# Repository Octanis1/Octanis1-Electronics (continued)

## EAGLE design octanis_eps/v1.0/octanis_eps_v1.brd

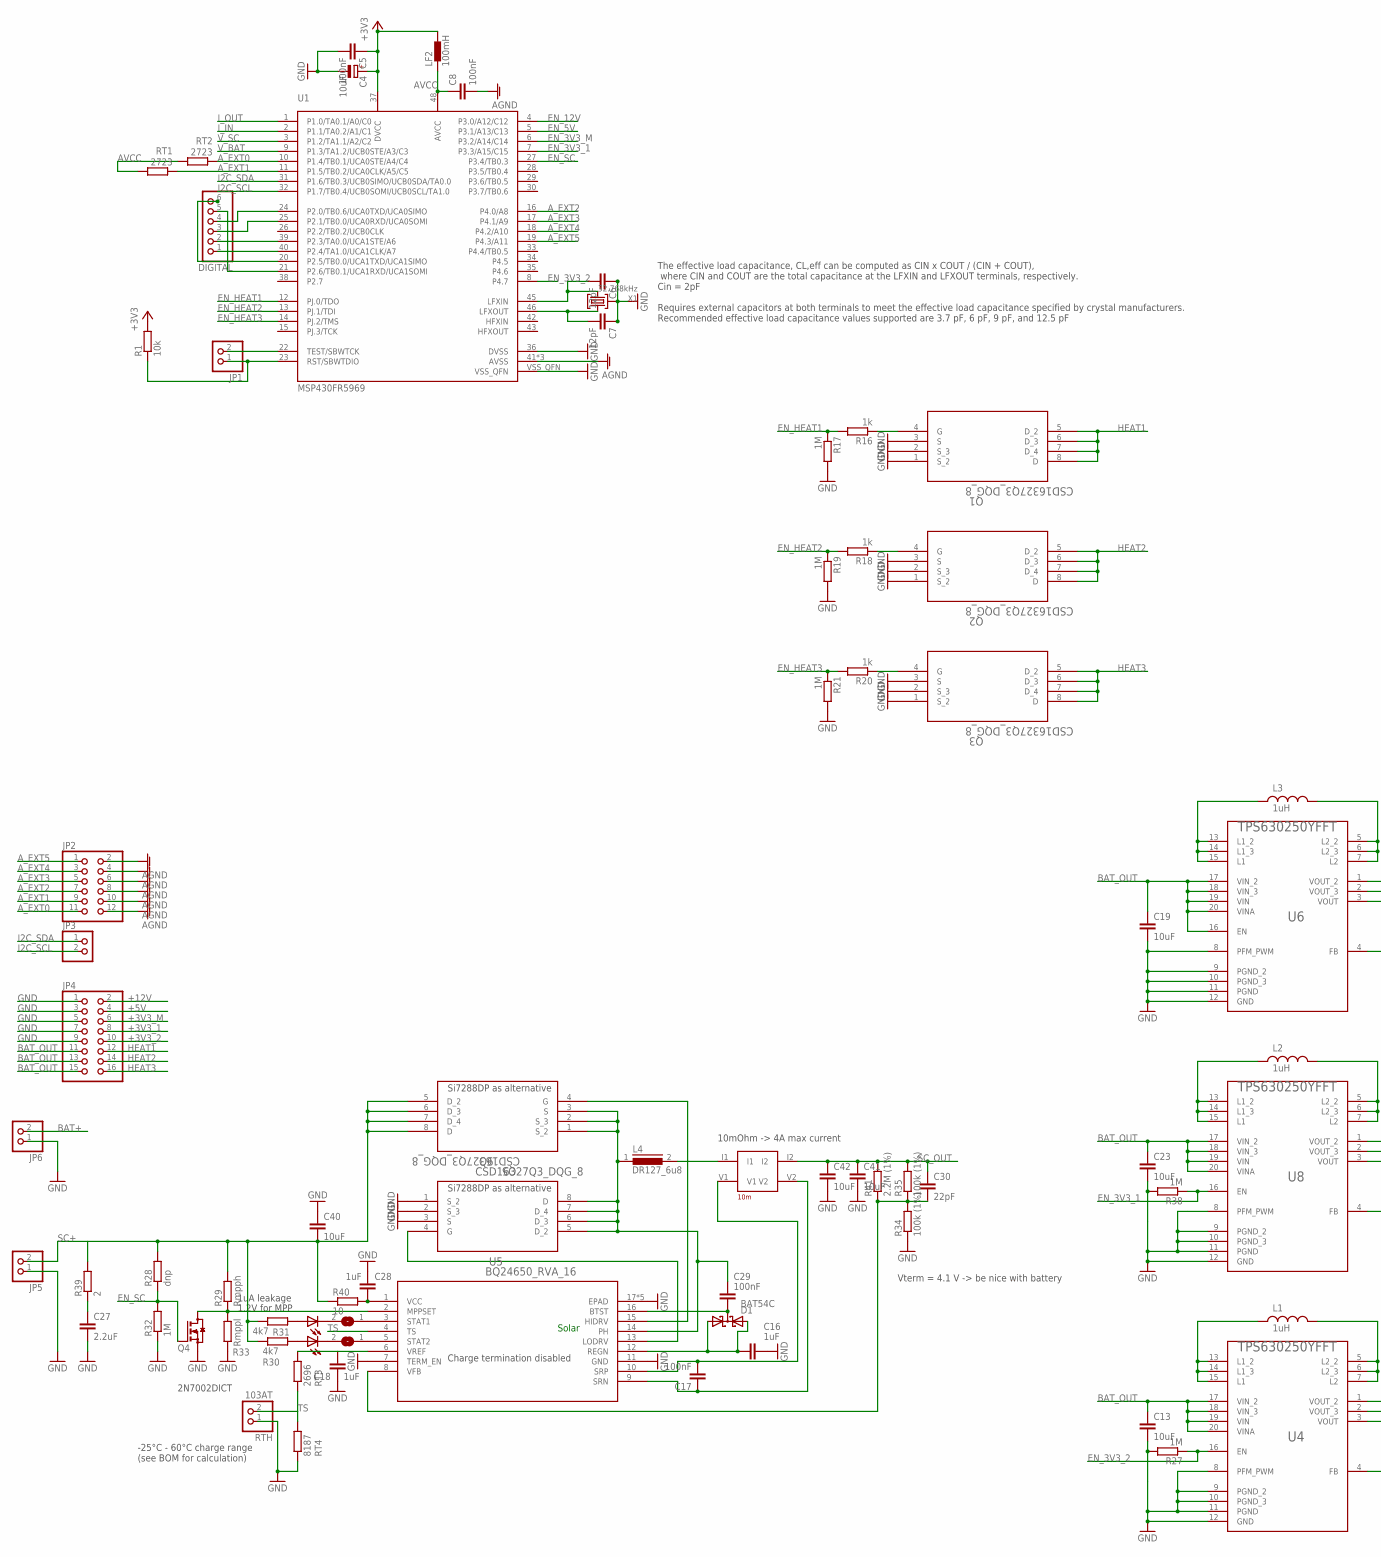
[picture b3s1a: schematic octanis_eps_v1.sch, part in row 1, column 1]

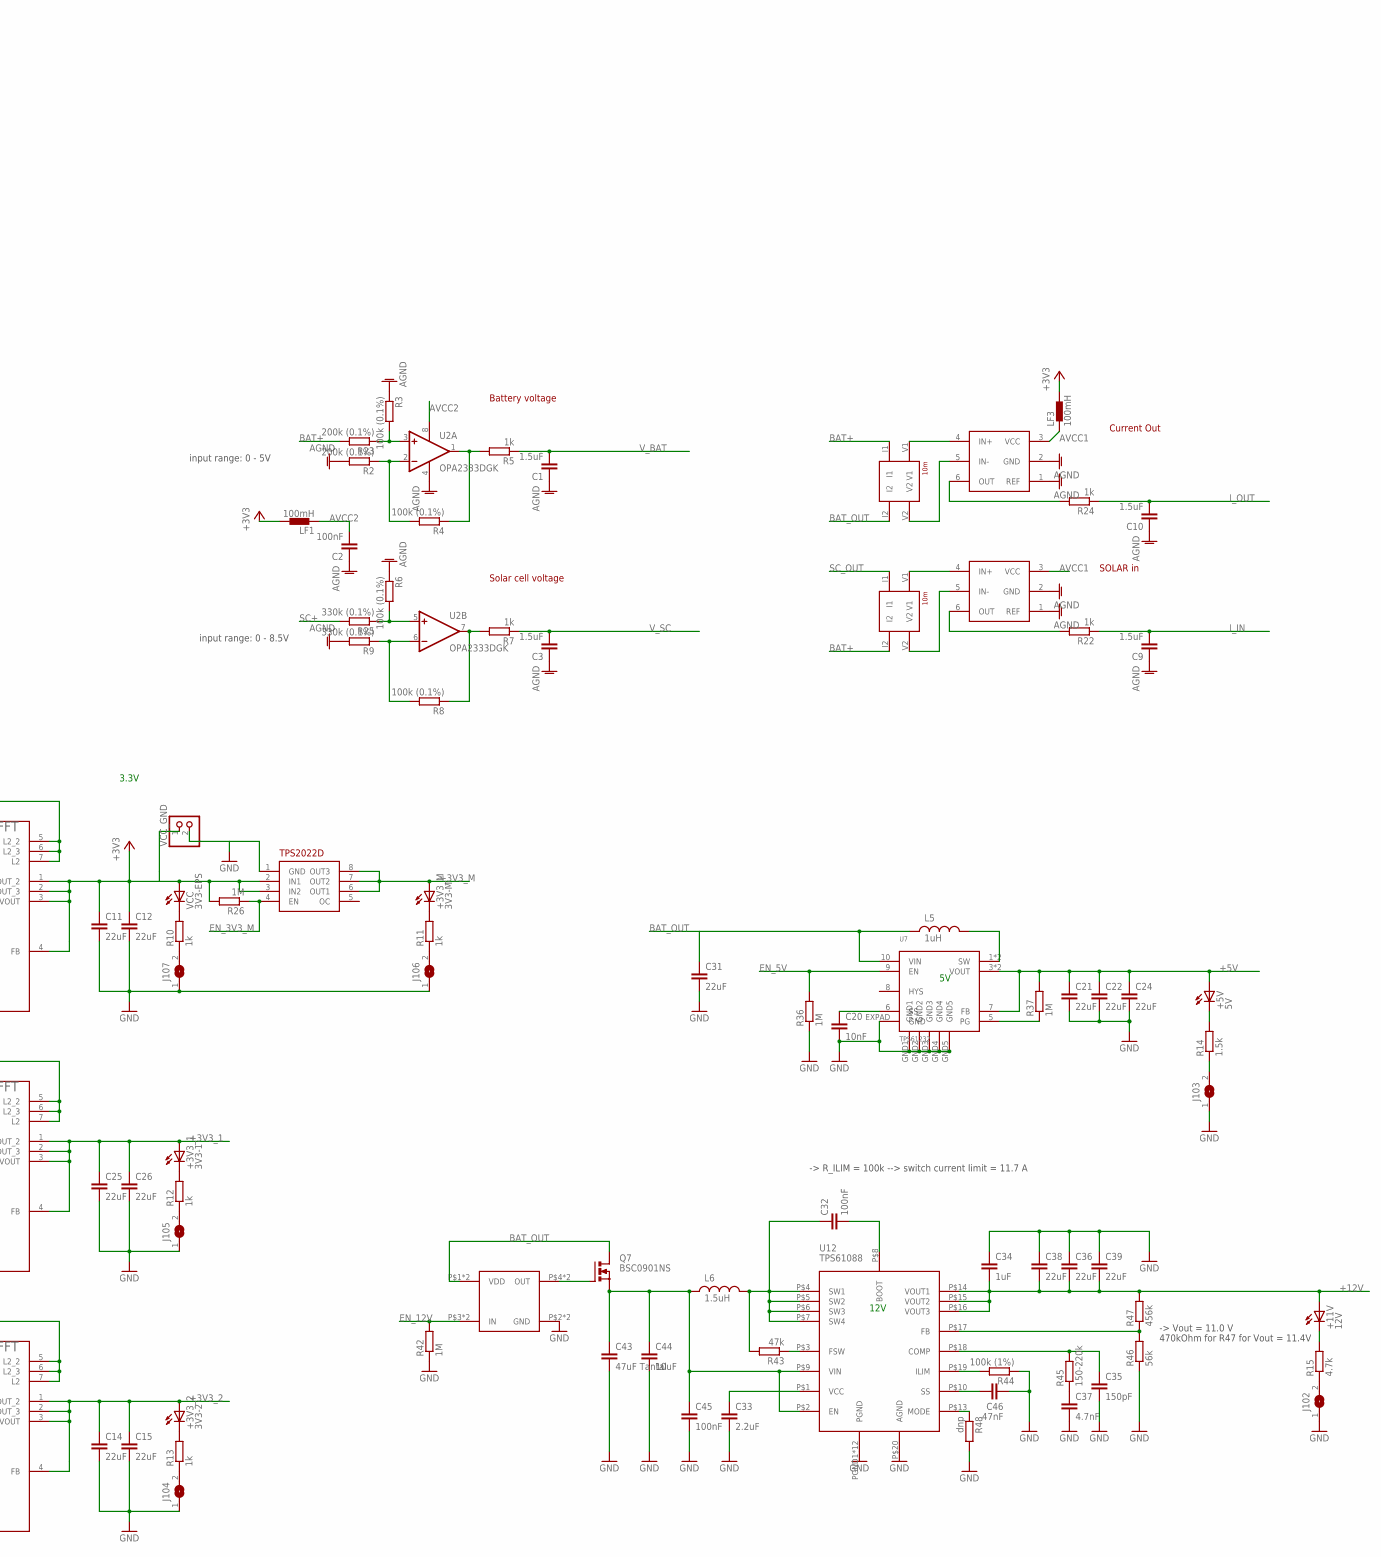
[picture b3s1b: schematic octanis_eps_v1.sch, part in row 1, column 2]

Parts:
+3V3_1: 3V3-1; CHIPLED_0603
+3V3_2: 3V3-2; CHIPLED_0603
+3V3_M: 3V3-M; CHIPLED_0603
+5V: 5V; CHIPLED_0603
+11V: 12V; CHIPLED_0603
C1, C3, C9, C10: 1.5uF; C0603
C2, C5, C8, C17, C29, C32, C45: 100nF; C0603
C4: 10uF; A/3216-18R
C6, C7: 12pF; C0603
C11, C12, C14, C15, C21, C22, C24, C25, C26, C36, C38, C39: 22uF; C0805
C13, C19, C23, C40, C41, C42, C44: 10uF; C0805
C16, C18, C28, C34: 1uF; C0603
C20: 10nF; C0603
C27, C33: 2.2uF; C0603
C30: 22pF; C0603
C31: 22uF; C0603
C35: 150pF; C0603
C37: 4.7nF; C0603
C43: 47uF Tantal; C1210
C46: 47nF; C0603
D1: BAT54C; SOT23
DIGITAL: PINHD-1X6B; 1X06-BIG
J100, J101, J102, J103, J104, J105, J106, J107: SJ
JP1, JP3, JP5, JP6: PINHD-1X2; 1X02
JP2: PINHD-2X6; 2X06
JP4: PINHD-2X8; 2X08
L1, L2, L3, L5: 1uH; XFL4020
L4: DR127_6u8; DR127
L6: 1.5uH; XFL4020
LF1, LF2, LF3: 100mH; 0402
Q1, Q2, Q3, Q5, Q6: CSD16327Q3_DQG_8; DQG8
Q4: BSS123; SOT23
Q7: BSC0901NS; PG-TDSON-8
R1: 10k; R0603
R2, R23: 200k (0.1%); R0603
R3, R4, R6, R8: 100k (0.1%); R0603
R5, R7, R10, R11, R12, R13, R16, R18, R20, R22, R24: 1k; R0603
R9, R25: 330k (0.1%); R0603
R14: 1.5k; R0603
R15: 4.7k; R0603
R17, R19, R21, R26, R27, R32, R36, R37, R38, R42: 1M; R0603
R28, R48: dnp; R0603
R29: Rmpph; R0603
R30, R31: 4k7; R0603
R33: Rmppl; R0603
R34, R35, R44: 100k (1%); R0603
R39: 2; R2010
R40: 10; R1206
R41: 2.2M (1%); R0603
R43: 47k; R0603
R45: 150-220k; R0603
R46: 56k; R0603
R47: 456k; R0603
RS1, RS2, RS3: 10m; 4PADS_RESISTOR
RT1, RT2: 2723; R0603
RT3: 2696; R0603
RT4: 8187; R0603
RTH: 103AT; 1X02
STAT1, STAT2: 5V-ok; CHIPLED_0603
U1: MSP430FR5969; S-PVQFN-N48
U2: OPA2333DGK; MSOP08
U3: TPS2022D; SO8
U4, U6, U8: TPS630250YFFT; YFF0020AEBA
U5: BQ24650_RVA_16; RVA16_2P14X2P14
U7: TPS61232; S-PVSON-N10
U9, U10: INA213; SC70-6
U11: MIC5019; QFN-4
U12: TPS61088; R-PVQFN-N20
VCC: 3V3-EPS; CHIPLED_0603
VCC_GND: PINHD-1X2; 1X02
X1: 32.768kHz; MS3V-T1R

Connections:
+3V3: C4.+, C5.1, C11.1, C12.1, LF1.2, LF2.2, LF3.2, R1.2, R26.2, U1.37 (DVCC), U3.2 (IN1), U3.3 (IN2), U6.1 (VOUT_2), U6.2 (VOUT_3), U6.3 (VOUT), U6.4 (FB), VCC.A, VCC_GND.1
+3V3_1: +3V3_1.A, C25.1, C26.1, JP4.8, U8.1 (VOUT_2), U8.2 (VOUT_3), U8.3 (VOUT), U8.4 (FB)
+3V3_2: +3V3_2.A, C14.1, C15.1, JP4.10, U4.1 (VOUT_2), U4.2 (VOUT_3), U4.3 (VOUT), U4.4 (FB)
+3V3_M: +3V3_M.A, JP4.6, U3.6 (OUT1), U3.7 (OUT2), U3.8 (OUT3)
+5V: +5V.A, C21.1, C22.1, C24.1, JP4.4, R37.2, U7.3 (VOUT), U7.4 (VOUT), U7.7 (FB)
+12V: +11V.A, C34.2, C36.2, C38.2, C39.2, JP4.2, R47.2, U12.P$14 (VOUT1), U12.P$15 (VOUT2), U12.P$16 (VOUT3)
AGND: C1.1, C2.1, C3.1, C8.2, C9.1, C10.1, JP2.2, JP2.4, JP2.6, JP2.8, JP2.10, JP2.12, R2.2, R3.1, R6.1, R9.2, U1.41 (AVSS), U1.44 (AVSS), U1.47 (AVSS), U2.4 (V-), U9.1 (REF), U9.2 (GND), U10.1 (REF), U10.2 (GND)
AVCC: C8.1, LF2.1, RT1.1, RT2.1, U1.48 (AVCC)
AVCC1: LF3.1, U9.3 (VCC), U10.3 (VCC)
AVCC2: C2.2, LF1.1, U2.8 (V+)
A_EXT0: JP2.11, RT2.2, U1.10 (P1.4/TB0.1/UCA0STE/A4/C4)
A_EXT1: JP2.9, RT1.2, U1.11 (P1.5/TB0.2/UCA0CLK/A5/C5)
A_EXT2: JP2.7, U1.16 (P4.0/A8)
A_EXT3: JP2.5, U1.17 (P4.1/A9)
A_EXT4: JP2.3, U1.18 (P4.2/A10)
A_EXT5: JP2.1, U1.19 (P4.3/A11)
BAT+: JP6.2, R23.2, RS2.I2, RS3.I1
BAT_11V: C43.1, C44.1, C45.1, L6.P$1 (1), Q7.1 (S), Q7.2 (S), Q7.3 (S), U12.P$2 (EN), U12.P$9 (VIN)
BAT_OUT: C13.1, C19.1, C23.1, C31.1, JP4.11, JP4.13, JP4.15, L5.P$1 (1), Q7.5 (D), Q7.6 (D), Q7.7 (D), Q7.8 (D), RS3.I2, U4.17 (VIN_2), U4.18 (VIN_3), U4.19 (VIN), U4.20 (VINA), U6.16 (EN), U6.17 (VIN_2), U6.18 (VIN_3), U6.19 (VIN), U6.20 (VINA), U7.10 (VIN), U8.17 (VIN_2), U8.18 (VIN_3), U8.19 (VIN), U8.20 (VINA), U11.P1 (VDD), U11.P$1 (VDD)
EN_3V3_1: R38.1, U1.7 (P3.3/A15/C15), U8.16 (EN)
EN_3V3_2: R27.1, U1.8 (P4.7), U4.16 (EN)
EN_3V3_M: R26.1, U1.6 (P3.2/A14/C14), U3.4 (EN)
EN_5V: R36.2, U1.5 (P3.1/A13/C13), U7.9 (EN)
EN_12V: R42.2, U1.4 (P3.0/A12/C12), U11.P3 (IN), U11.P$3 (IN)
EN_HEAT1: R16.2, R17.1, U1.12 (PJ.0/TDO)
EN_HEAT2: R18.2, R19.1, U1.13 (PJ.1/TDI)
EN_HEAT3: R20.2, R21.1, U1.14 (PJ.2/TMS)
EN_SC: Q4.1 (G), R28.1, R32.2, U1.27 (P3.4/TB0.3)
GND: C4.-, C5.2, C6.1, C7.1, C11.2, C12.2, C13.2, C14.2, C15.2, C16.2, C18.2, C19.2, C20.2, C21.2, C22.2, C23.2, C24.2, C25.2, C26.2, C27.2, C28.2, C31.2, C33.2, C34.1, C35.2, C36.1, C37.2, C38.1, C39.1, C40.1, C41.2, C42.2, C43.2, C44.2, C45.2, C46.2, J102.1, J103.1, J104.1, J105.1, J106.1, J107.1, JP4.1, JP4.3, JP4.5, JP4.7, JP4.9, JP5.1, JP6.1, Q1.1 (S_2), Q1.2 (S_3), Q1.3 (S), Q2.1 (S_2), Q2.2 (S_3), Q2.3 (S), Q3.1 (S_2), Q3.2 (S_3), Q3.3 (S), Q4.2 (S), Q6.1 (S_2), Q6.2 (S_3), Q6.3 (S), R17.2, R19.2, R21.2, R27.2, R32.1, R33.1, R34.1, R36.1, R38.2, R42.1, R44.1, R46.1, R48.2, RT4.2, RTH.1, U1.36 (DVSS), U1.VSS_QFN, U3.1 (GND), U4.8 (PFM_PWM), U4.9 (PGND_2), U4.10 (PGND_3), U4.11 (PGND), U4.12 (GND), U5.7 (TERM_EN), U5.11 (GND), U5.17 (EPAD), U5.V (EPAD), U5.V_1 (EPAD), U5.V_2 (EPAD), U5.V_3 (EPAD), U6.8 (PFM_PWM), U6.9 (PGND_2), U6.10 (PGND_3), U6.11 (PGND), U6.12 (GND), U7.EXPAD (GND), U7.GND1, U7.GND2, U7.GND3, U7.GND4, U7.GND5, U8.8 (PFM_PWM), U8.9 (PGND_2), U8.10 (PGND_3), U8.11 (PGND), U8.12 (GND), U11.P2 (GND), U11.P$2 (GND), U12.P$20 (AGND), U12.PGND1 (PGND), U12.PGND2 (PGND), U12.PGND3 (PGND), U12.PGND4 (PGND), U12.PGND5 (PGND), U12.PGND6 (PGND)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
HEAT1: JP4.12, Q1.5 (D_2), Q1.6 (D_3), Q1.7 (D_4), Q1.8 (D)
HEAT2: JP4.14, Q2.5 (D_2), Q2.6 (D_3), Q2.7 (D_4), Q2.8 (D)
HEAT3: JP4.16, Q3.5 (D_2), Q3.6 (D_3), Q3.7 (D_4), Q3.8 (D)
I2C_SCL: JP3.2, U1.32 (P1.7/TB0.4/UCB0SOMI/UCB0SCL/TA1.0)
I2C_SDA: JP3.1, U1.31 (P1.6/TB0.3/UCB0SIMO/UCB0SDA/TA0.0)
IND: L5.P$2 (2), U7.1 (SW), U7.2 (SW)
I_IN: C9.2, R22.1, U1.2 (P1.1/TA0.2/A1/C1)
I_OUT: C10.2, R24.1, U1.1 (P1.0/TA0.1/A0/C0)
LED5: +5V.C, R14.2
unnamed: L3.P$1 (1), U6.13 (L1_2), U6.14 (L1_3), U6.15 (L1)
unnamed: R37.1, U7.5 (PG)
unnamed: L3.P$2 (2), U6.5 (L2_2), U6.6 (L2_3), U6.7 (L2)
unnamed: L4.2, RS1.I1
unnamed: C20.1, U7.6 (SS)
unnamed: L2.P$1 (1), U8.13 (L1_2), U8.14 (L1_3), U8.15 (L1)
unnamed: L2.P$2 (2), U8.5 (L2_2), U8.6 (L2_3), U8.7 (L2)
unnamed: R48.1, U12.P$13 (MODE)
unnamed: Q7.4 (G), U11.P4 (OUT), U11.P$4 (OUT)
unnamed: L1.P$1 (1), U4.13 (L1_2), U4.14 (L1_3), U4.15 (L1)
unnamed: L1.P$2 (2), U4.5 (L2_2), U4.6 (L2_3), U4.7 (L2)
unnamed: JP1.1, R1.1, U1.23 (RST/SBWTDIO)
unnamed: J103.2, R14.1
unnamed: JP1.2, U1.22 (TEST/SBWTCK)
unnamed: C7.2, U1.46 (LFXOUT), X1.P1 (1)
unnamed: C6.2, U1.45 (LFXIN), X1.P2 (2)
unnamed: DIGITAL.3, U1.25 (P2.1/TB0.0/UCA0RXD/UCA0SOMI)
unnamed: R4.1, R5.2, U2.1 (OUT)
unnamed: R2.1, R4.2, U2.2 (-IN)
unnamed: R3.2, R23.1, U2.3 (+IN)
unnamed: R7.2, R8.1, U2.7 (OUT)
unnamed: R8.2, R9.1, U2.6 (-IN)
unnamed: R6.2, R25.1, U2.5 (+IN)
unnamed: R24.2, U10.6 (OUT)
unnamed: R22.2, U9.6 (OUT)
unnamed: Q3.4 (G), R20.1
unnamed: DIGITAL.4, U1.24 (P2.0/TB0.6/UCA0TXD/UCA0SIMO)
unnamed: DIGITAL.2, U1.39 (P2.3/TA0.0/UCA1STE/A6)
unnamed: DIGITAL.1, U1.40 (P2.4/TA1.0/UCA1CLK/A7)
unnamed: Q2.4 (G), R18.1
unnamed: RS3.V1, U10.4 (IN+)
unnamed: RS3.V2, U10.5 (IN-)
unnamed: RS2.V1, U9.4 (IN+)
unnamed: RS2.V2, U9.5 (IN-)
unnamed: DIGITAL.5, U1.21 (P2.6/TB0.1/UCA1RXD/UCA1SOMI)
unnamed: Q1.4 (G), R16.1
unnamed: C32.2, U12.P$8 (BOOT)
unnamed: +3V3_M.C, R11.2
unnamed: J106.2, R11.1
unnamed: DIGITAL.6, U1.20 (P2.5/TB0.0/UCA1TXD/UCA1SIMO)
unnamed: C27.1, R39.1
unnamed: R10.2, VCC.C
unnamed: J107.2, R10.1
unnamed: +3V3_2.C, R13.2
unnamed: J104.2, R13.1
unnamed: +11V.C, R15.2
unnamed: J102.2, R15.1
unnamed: C32.1, L6.P$2 (2), R43.2, U12.P$4 (SW1), U12.P$5 (SW2), U12.P$6 (SW3), U12.P$7 (SW4)
unnamed: +3V3_1.C, R12.2
unnamed: J105.2, R12.1
unnamed: R43.1, U12.P$3 (FSW)
unnamed: C37.1, R45.1
unnamed: C46.1, U12.P$10 (SS)
unnamed: R44.2, U12.P$19 (ILIM)
unnamed: C35.1, R45.2, U12.P$18 (COMP)
unnamed: C33.1, U12.P$1 (VCC)
unnamed: R46.2, R47.1, U12.P$17 (FB)
unnamed: Q4.3 (D), R29.1, R33.2, U5.2 (MPPSET)
unnamed: R31.1, STAT1.A
unnamed: J101.2, STAT2.C
unnamed: J100.2, STAT1.C
unnamed: R30.1, STAT2.A
unnamed: J101.1, U5.5 (STAT2)
unnamed: J100.1, U5.3 (STAT1)
unnamed: C18.1, RT3.1, U5.6 (VREF)
unnamed: C28.1, R40.2, U5.1 (VCC)
unnamed: C29.1, L4.1, Q5.1 (S_2), Q5.2 (S_3), Q5.3 (S), Q6.5 (D_2), Q6.6 (D_3), Q6.7 (D_4), Q6.8 (D), U5.14 (PH)
unnamed: C17.2, RS1.V1, U5.10 (SRP)
unnamed: C17.1, RS1.V2, U5.9 (SRN)
unnamed: Q5.4 (G), U5.15 (HIDRV)
unnamed: Q6.4 (G), U5.13 (LODRV)
unnamed: C30.2, R34.2, R35.1, R41.1, U5.8 (VFB)
unnamed: C16.1, D1.1 (A1), D1.2 (A2), U5.12 (REGN)
unnamed: C29.2, D1.3 (CC), U5.16 (BTST)
SC+: C40.2, JP5.2, Q5.5 (D_2), Q5.6 (D_3), Q5.7 (D_4), Q5.8 (D), R25.2, R28.2, R29.2, R30.2, R31.2, R39.2, R40.1
SC_OUT: C30.1, C41.1, C42.1, R35.2, R41.2, RS1.I2, RS2.I1
TS: RT3.2, RT4.1, RTH.2, U5.4 (TS)
V_BAT: C1.2, R5.1, U1.9 (P1.3/TA1.2/UCB0STE/A3/C3)
V_SC: C3.2, R7.1, U1.3 (P1.2/TA1.1/A2/C2)

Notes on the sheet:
Solar
3.3V
12V
Battery voltage
Solar cell voltage
SOLAR in
Current Out
-> Vout = 11.0 V
470kOhm for R47 for Vout = 11.4V
1.2V for MPP
1uA leakage
Charge termination disabled
Vterm = 4.1 V -> be nice with battery
10mOhm -> 4A max current
2N7002DICT
Si7288DP as alternative
-> R_ILIM = 100k --> switch current limit = 11.7 A
The effective load capacitance, CL,eff can be computed as CIN x COUT / (CIN + COUT), where CIN and COUT are the total capacitance at the LFXIN and LFXOUT terminals, respectively. Cin = 2pF Requires external capacitors at both terminals to meet the effective load capacitance specified by crystal man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
input range: 0 - 8.5V
input range: 0 - 5V
-25°C - 60°C charge range (see BOM for calculation)

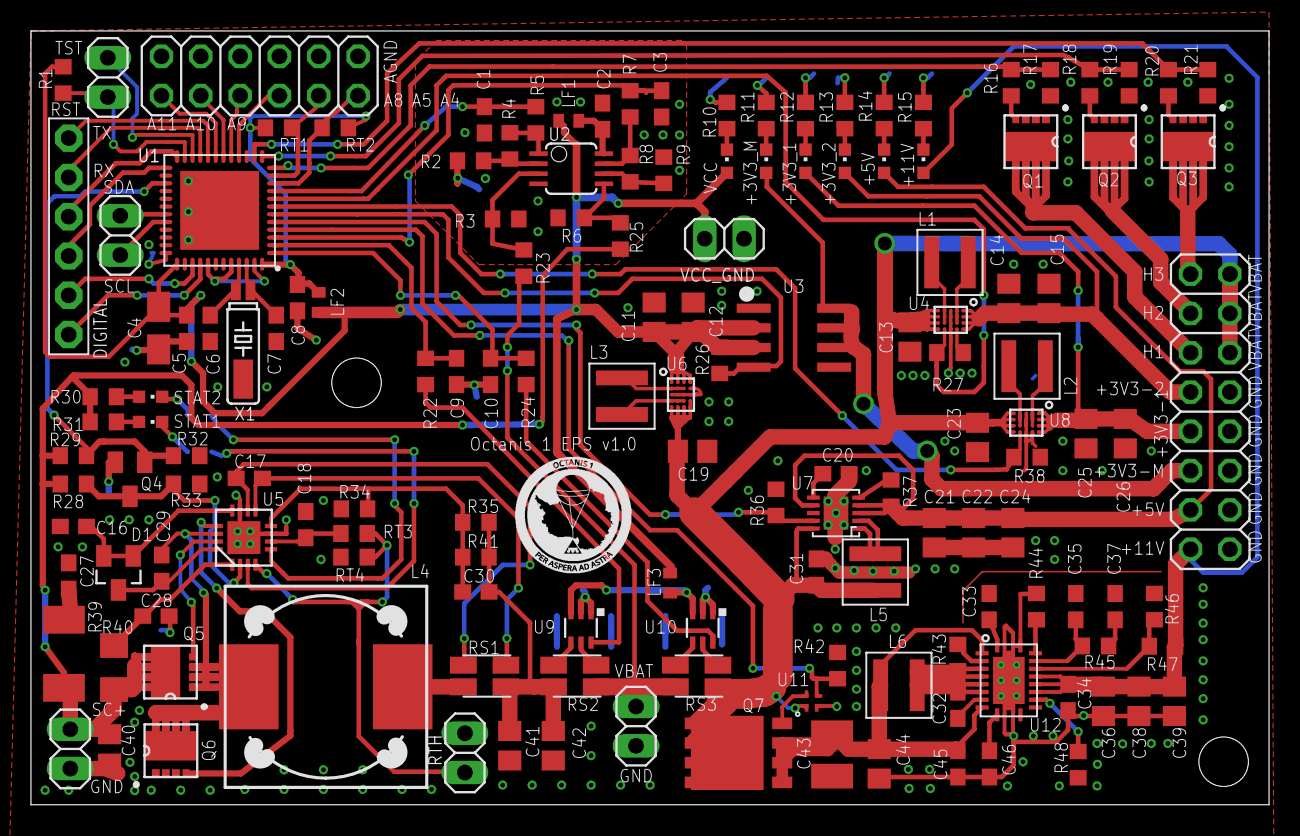
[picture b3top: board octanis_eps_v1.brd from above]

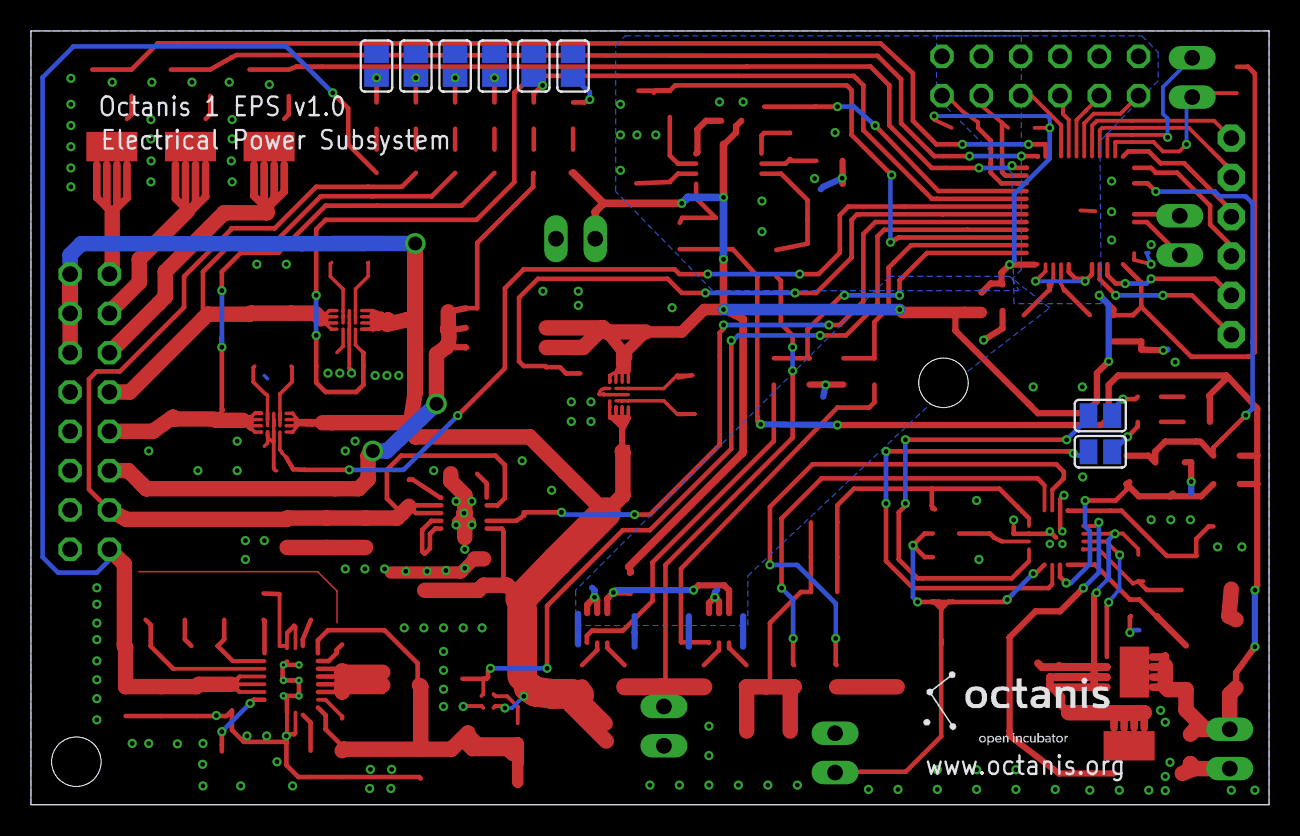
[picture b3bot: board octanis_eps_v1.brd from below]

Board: 2 copper layers, 80.0 x 50.0 mm, 156 parts (8 on the bottom side), 117 nets.

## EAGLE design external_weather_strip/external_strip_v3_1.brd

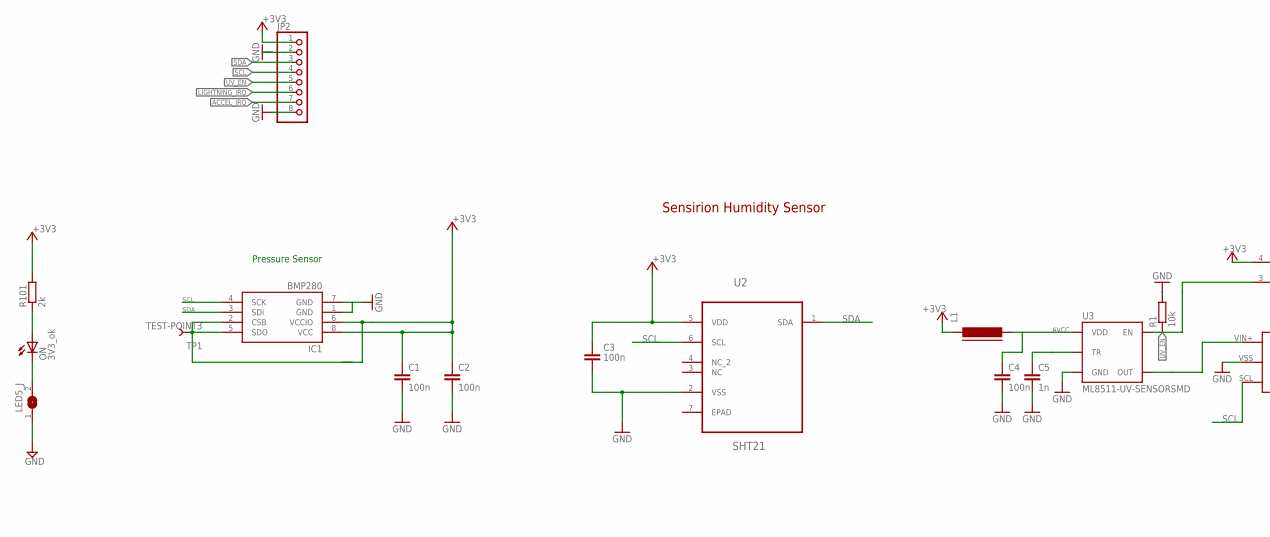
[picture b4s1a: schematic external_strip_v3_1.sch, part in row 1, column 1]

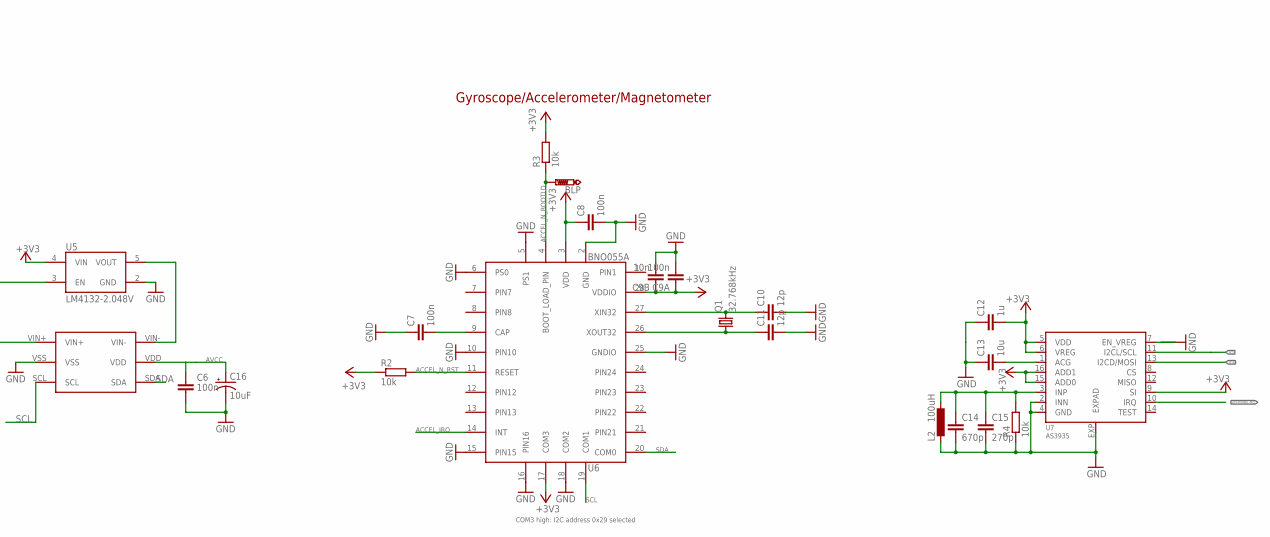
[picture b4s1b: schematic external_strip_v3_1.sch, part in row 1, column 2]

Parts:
BLP: PTR1B1,27; B1,27
C1, C2, C3, C6, C7, C8, C9A: 100n; C0603
C4: 100n; 0603-CAP
C5: 1n; 0603-CAP
C9B: 10n; C0603
C10, C11: 12p; C0603
C12: 1u; C0603
C13: 10u; C0603
C14: 670p; C0603
C15: 270p; C0603
C16: 10uF; EIA3216
IC1: BMP280; LGA8
JP2: PINHD-1X8; 1X08
L1: FERRITE-0603; FB603
L2: 100uH; COILCRAFT
LED5_J: SJ
ON: 3V3_ok; CHIPLED_0603
Q1: 32.768kHz; FC-12M
R1, R2, R3, R4: 10k; R0603
R101: 2k; R0603
TP1: TEST-POINT3; PAD.03X.03
U2: SHT21; DFN300X300X110-7N
U3: ML8511-UV-SENSORSMD; ML8511
U4: MCP3425; SOT-23-6
U5: LM4132-2.048V; SOT23-5
U6: BNO055A; BNO055
U7: AS3935; 16LDMLPQ

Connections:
+3V3: C1.1, C2.1, C3.1, C8.1, C9A.1, C9B.1, C12.2, IC1.2 (CSB), IC1.5 (SDO), IC1.6 (VCCIO), IC1.8 (VCC), JP2.1, L1.1, R2.1, R3.2, R101.2, TP1.P$1, U2.5 (VDD), U5.4 (VIN), U6.3 (VDD), U6.17 (COM3), U6.28 (VDDIO), U7.5 (VDD), U7.6 (VREG), U7.9 (SI), U7.15 (ADD0), U7.16 (ADD1)
ACCEL_IRQ: JP2.7, U6.14 (INT)
ACCEL_N_BOOTLD: BLP.TP, R3.1, U6.4 (BOOT_LOAD_PIN)
ACCEL_N_RST: R2.2, U6.11 (RESET)
AVCC: C4.1, C6.1, C16.A (+), L1.2, U3.7 (VDD), U4.VDD
GND: C1.2, C2.2, C3.2, C4.2, C5.2, C6.2, C7.1, C8.2, C9A.2, C9B.2, C10.2, C11.2, C12.1, C13.1, C14.2, C15.2, C16.C (-), IC1.1 (GND), IC1.7 (GND), JP2.2, JP2.8, L2.2, LED5_J.1, R1.2, R4.1, U2.2 (VSS), U3.5 (GND), U4.VSS, U5.2 (GND), U6.2 (GND), U6.5 (PS1), U6.6 (PS0), U6.10 (PIN10), U6.15 (PIN15), U6.16 (PIN16), U6.18 (COM2), U6.25 (GNDIO), U7.2 (INN), U7.4 (GND), U7.7 (EN_VREG), U7.EXP (EXPAD)
LIGHTNING_IRQ: JP2.6, U7.10 (IRQ)
unnamed: U3.8 (OUT), U4.VIN+
unnamed: C13.2, U7.1 (ACG)
unnamed: C5.1, U3.9 (TR)
unnamed: LED5_J.2, ON.C
unnamed: C14.1, C15.1, L2.1, R4.2, U7.3 (INP)
unnamed: U4.VIN-, U5.5 (VOUT)
unnamed: ON.A, R101.1
unnamed: C7.2, U6.9 (CAP)
unnamed: C10.1, Q1.2, U6.27 (XIN32)
unnamed: C11.1, Q1.1, U6.26 (XOUT32)
SCL: IC1.4 (SCK), JP2.4, U2.6 (SCL), U4.SCL, U6.19 (COM1), U7.11 (I2CL/SCL)
SDA: IC1.3 (SDI), JP2.3, U2.1 (SDA), U4.SDA, U6.20 (COM0), U7.13 (I2CD/MOSI)
UV_EN: JP2.5, R1.1, U3.4 (EN), U5.3 (EN)

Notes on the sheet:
Sensirion Humidity Sensor
Pressure Sensor
Gyroscope/Accelerometer/Magnetometer
COM3 high: I2C address 0x29 selected

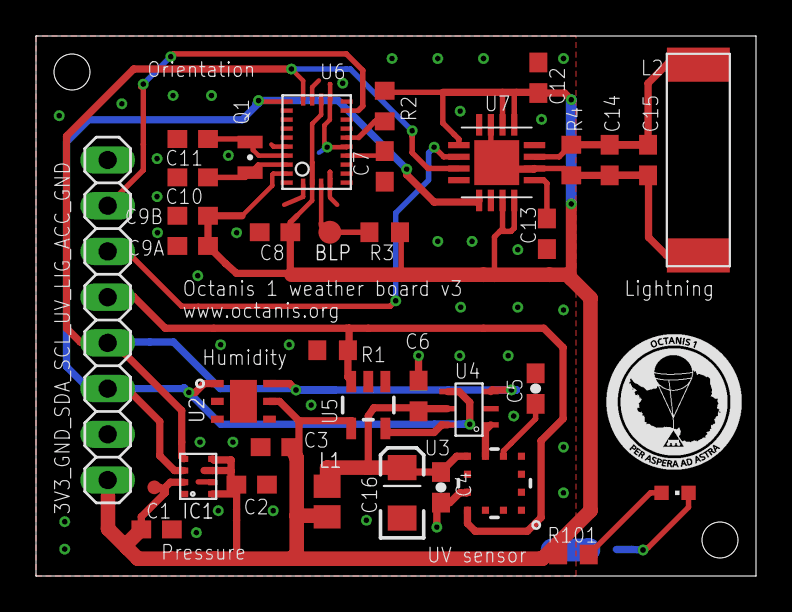
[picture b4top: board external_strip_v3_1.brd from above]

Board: 2 copper layers, 40.0 x 30.0 mm, 37 parts (1 on the bottom side), 20 nets.

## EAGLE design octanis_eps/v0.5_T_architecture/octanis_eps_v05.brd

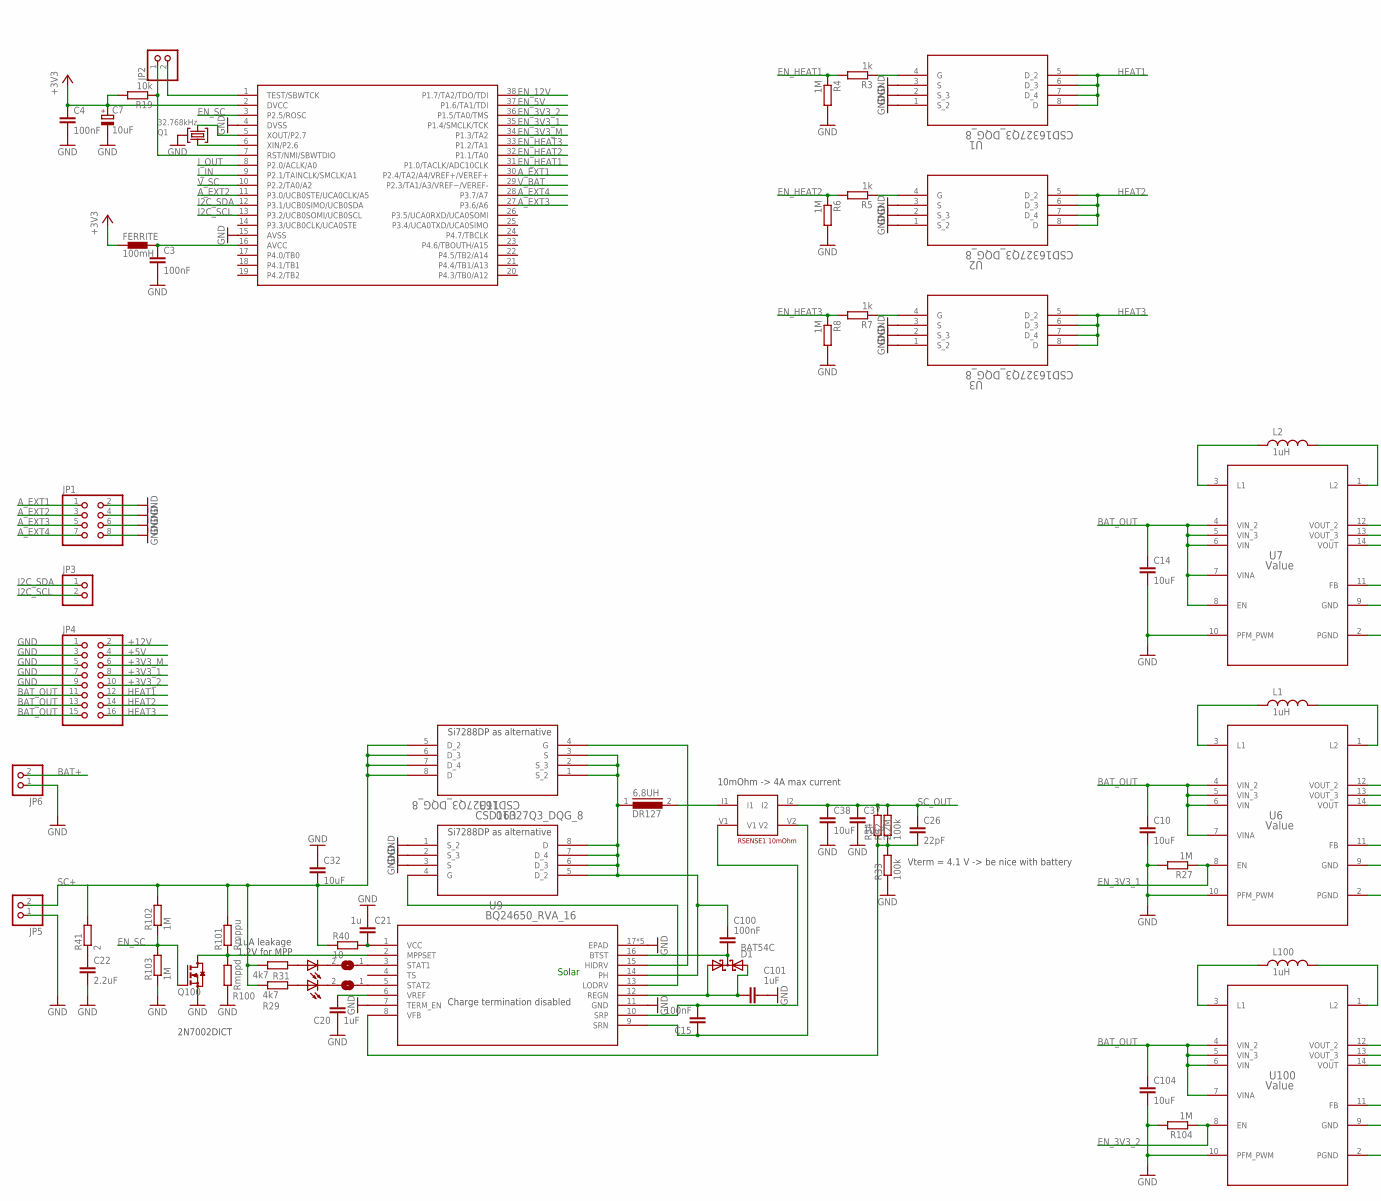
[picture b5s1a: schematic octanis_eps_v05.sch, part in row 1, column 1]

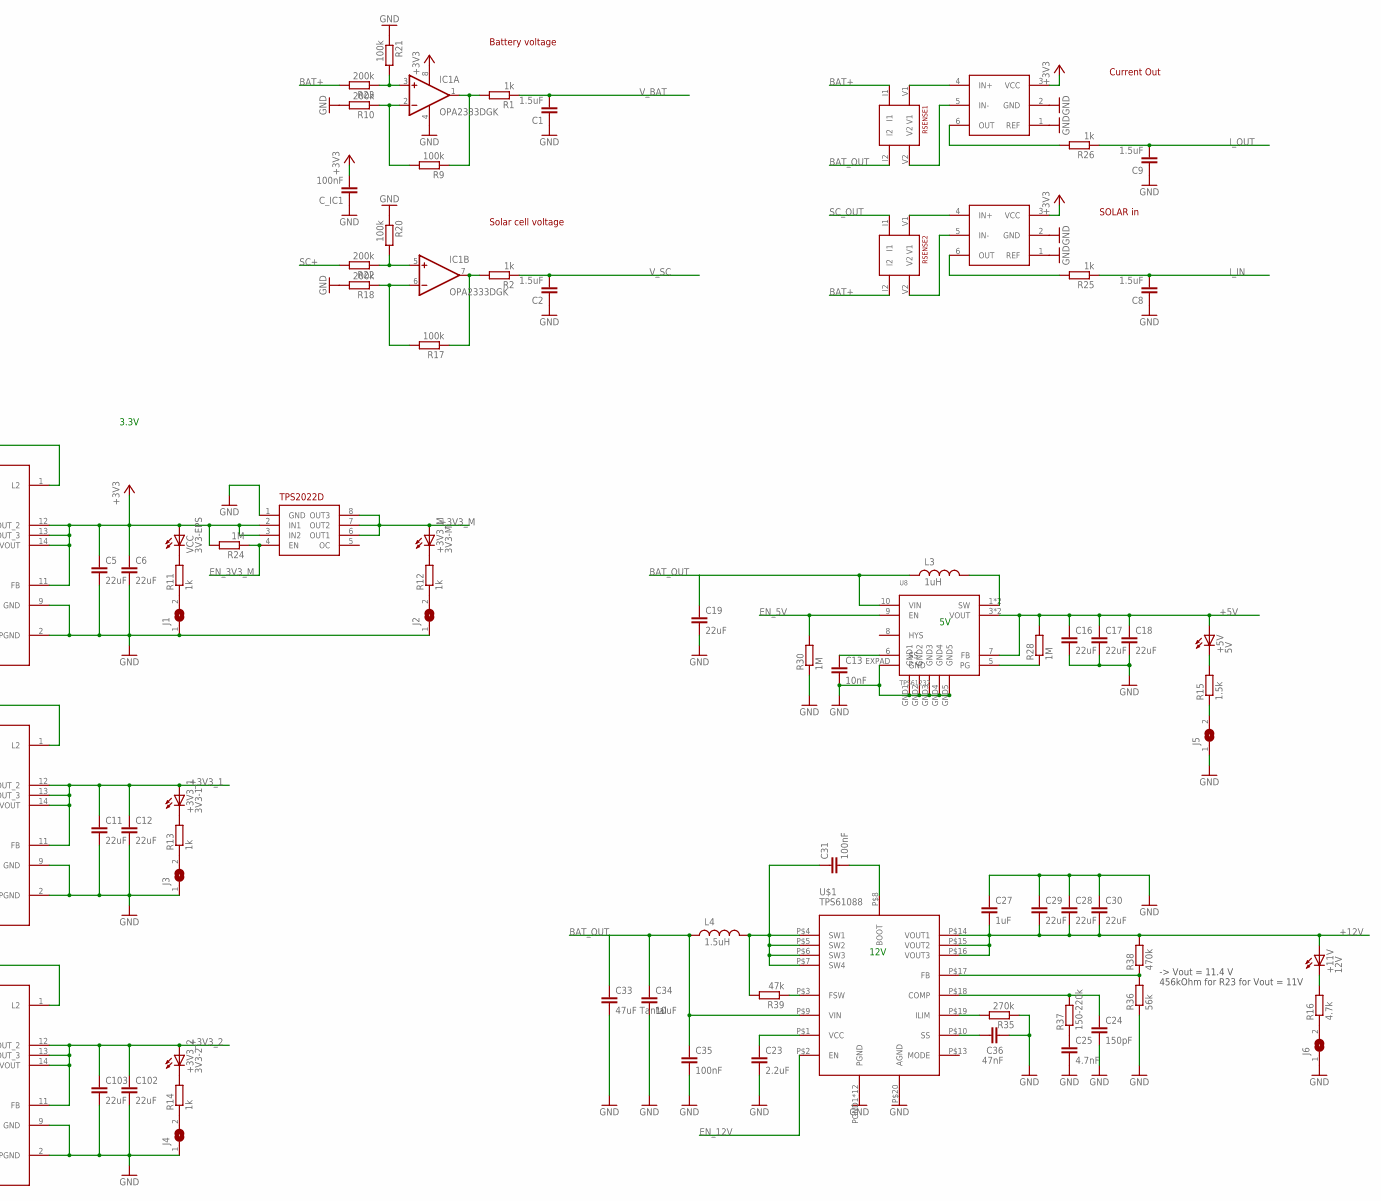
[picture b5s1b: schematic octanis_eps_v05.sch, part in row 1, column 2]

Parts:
6.8UH: DR127
+3V3_1: 3V3-1; CHIPLED_0603
+3V3_2: 3V3-2; CHIPLED_0603
+3V3_M: 3V3-M; CHIPLED_0603
+5V: 5V; CHIPLED_0603
+11V: 12V; CHIPLED_0603
C1, C2, C8, C9: 1.5uF; C0603
C3, C4, C15, C31, C35, C100: 100nF; C0603
C5, C6, C11, C12, C16, C17, C18, C28, C29, C30, C102, C103: 22uF; C0805
C7: 10uF; A/3216-18R
C10, C14, C32, C34, C37, C38, C104: 10uF; C0805
C13: 10nF; C0603
C19: 22uF; C0603
C20, C27, C101: 1uF; C0603
C21: 1u; C0603
C22, C23: 2.2uF; C0603
C24: 150pF; C0603
C25: 4.7nF; C0603
C26: 22pF; C0603
C33: 47uF Tantal; C1210
C36: 47nF; C0603
C_IC1: 100nF; C0603
D1: BAT54C; SOT23
FERRITE: 100mH; 0402
IC1: OPA2333DGK; MSOP08
J1, J2, J3, J4, J5, J6, J7, J8: SJ
JP1: PINHD-2X4; 2X04
JP2, JP3, JP5, JP6: PINHD-1X2; 1X02
JP4: PINHD-2X8; 2X08
L1, L2, L3, L100: 1uH; XFL4020
L4: 1.5uH; XFL4020
Q1: 32.768kHz; MS3V-T1R
Q100: BSS123; SOT23
R1, R2, R3, R5, R7, R11, R12, R13, R14, R25, R26: 1k; R0603
R4, R6, R8, R24, R27, R28, R30, R102, R103, R104: 1M; R0603
R9, R17, R20, R21, R32, R33: 100k; R0603
R10, R18, R22, R23: 200k; R0603
R15: 1.5k; R0603
R16: 4.7k; R0603
R19: 10k; R0603
R29, R31: 4k7; R0603
R34: 2.2M; R0603
R35: 270k; R0603
R36: 56k; R0603
R37: 150-220k; R0603
R38: 470k; R0603
R39: 47k; R0603
R40: 10; R1206
R41: 2; R2012
R100: Rmppd; R0603
R101: Rmppu; R0603
RSENSE1: RSENSE2; 4PADS_RESISTOR
R_SENSE1: RSENSE1 10mOhm; 4PADS_RESISTOR
R_SENSE2: RSENSE1; 4PADS_RESISTOR
STAT1, STAT2: 5V-ok; CHIPLED_0603
U1, U2, U3, U10, U11: CSD16327Q3_DQG_8; DQG8
U4: MSP430G2544; TSSOP38
U5: TPS2022D; SO8
U6, U7, U100: Value; RNC0014A
U8: TPS61232; S-PVSON-N10
U9: BQ24650_RVA_16; RVA16_2P14X2P14
U$1: TPS61088; R-PVQFN-N20
U$2, U$3: INA213; SC70-6
VCC: 3V3-EPS; CHIPLED_0603

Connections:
+3V3: C4.1, C5.1, C6.1, C7.+, C_IC1.2, FERRITE.1, IC1.8 (V+), R19.2, R24.2, U4.2 (DVCC), U5.2 (IN1), U5.3 (IN2), U7.11 (FB), U7.12 (VOUT_2), U7.13 (VOUT_3), U7.14 (VOUT), U$2.3 (VCC), U$3.3 (VCC), VCC.A
+3V3_1: +3V3_1.A, C11.1, C12.1, JP4.8, U6.11 (FB), U6.12 (VOUT_2), U6.13 (VOUT_3), U6.14 (VOUT)
+3V3_2: +3V3_2.A, C102.1, C103.1, JP4.10, U100.11 (FB), U100.12 (VOUT_2), U100.13 (VOUT_3), U100.14 (VOUT)
+3V3_M: +3V3_M.A, JP4.6, U5.6 (OUT1), U5.7 (OUT2), U5.8 (OUT3)
+5V: +5V.A, C16.1, C17.1, C18.1, JP4.4, R28.2, U8.3 (VOUT), U8.4 (VOUT), U8.7 (FB)
+12V: +11V.A, C27.2, C28.2, C29.2, C30.2, JP4.2, R38.2, U$1.P$14 (VOUT1), U$1.P$15 (VOUT2), U$1.P$16 (VOUT3)
A_EXT1: JP1.1, U4.30 (P2.4/TA2/A4/VREF+/VEREF+)
A_EXT2: JP1.3, U4.11 (P3.0/UCB0STE/UCA0CLK/A5)
A_EXT3: JP1.5, U4.27 (P3.6/A6)
A_EXT4: JP1.7, U4.28 (P3.7/A7)
BAT+: JP6.2, R23.2, RSENSE1.I2, R_SENSE2.I1
BAT_OUT: C10.1, C14.1, C19.1, C33.1, C34.1, C35.1, C104.1, JP4.11, JP4.13, JP4.15, L3.P$1 (1), L4.P$1 (1), R_SENSE2.I2, U6.4 (VIN_2), U6.5 (VIN_3), U6.6 (VIN), U6.7 (VINA), U7.4 (VIN_2), U7.5 (VIN_3), U7.6 (VIN), U7.7 (VINA), U7.8 (EN), U8.10 (VIN), U100.4 (VIN_2), U100.5 (VIN_3), U100.6 (VIN), U100.7 (VINA), U$1.P$9 (VIN)
EN_3V3_1: R27.1, U4.35 (P1.4/SMCLK/TCK), U6.8 (EN)
EN_3V3_2: R104.1, U4.36 (P1.5/TA0/TMS), U100.8 (EN)
EN_3V3_M: R24.1, U4.34 (P1.3/TA2), U5.4 (EN)
EN_5V: R30.2, U4.37 (P1.6/TA1/TDI), U8.9 (EN)
EN_12V: U4.38 (P1.7/TA2/TDO/TDI), U$1.P$2 (EN)
EN_HEAT1: R3.2, R4.1, U4.31 (P1.0/TACLK/ADC10CLK)
EN_HEAT2: R5.2, R6.1, U4.32 (P1.1/TA0)
EN_HEAT3: R7.2, R8.1, U4.33 (P1.2/TA1)
EN_SC: Q100.1 (G), R102.1, R103.2, U4.3 (P2.5/ROSC)
GND: C1.1, C2.1, C3.2, C4.2, C5.2, C6.2, C7.-, C8.1, C9.1, C10.2, C11.2, C12.2, C13.2, C14.2, C16.2, C17.2, C18.2, C19.2, C20.2, C21.2, C22.2, C23.2, C24.2, C25.2, C27.1, C28.1, C29.1, C30.1, C32.1, C33.2, C34.2, C35.2, C36.2, C37.2, C38.2, C101.2, C102.2, C103.2, C104.2, C_IC1.1, IC1.4 (V-), J1.1, J2.1, J3.1, J4.1, J5.1, J6.1, JP1.2, JP1.4, JP1.6, JP1.8, JP4.1, JP4.3, JP4.5, JP4.7, JP4.9, JP5.1, JP6.1, Q1.P3 (GND), Q100.2 (S), R4.2, R6.2, R8.2, R10.2, R18.2, R20.1, R21.1, R27.2, R30.1, R33.1, R35.1, R36.1, R100.1, R103.1, R104.2, U1.1 (S_2), U1.2 (S_3), U1.3 (S), U2.1 (S_2), U2.2 (S_3), U2.3 (S), U3.1 (S_2), U3.2 (S_3), U3.3 (S), U4.4 (DVSS), U4.15 (AVSS), U5.1 (GND), U6.2 (PGND), U6.9 (GND), U6.10 (PFM_PWM), U7.2 (PGND), U7.9 (GND), U7.10 (PFM_PWM), U8.EXPAD (GND), U8.GND1, U8.GND2, U8.GND3, U8.GND4, U8.GND5, U9.7 (TERM_EN), U9.11 (GND), U9.17 (EPAD), U9.V (EPAD), U9.V_1 (EPAD), U9.V_2 (EPAD), U9.V_3 (EPAD), U11.1 (S_2), U11.2 (S_3), U11.3 (S), U100.2 (PGND), U100.9 (GND), U100.10 (PFM_PWM), U$1.P$20 (AGND), U$1.PGND1 (PGND), U$1.PGND2 (PGND), U$1.PGND3 (PGND), U$1.PGND4 (PGND)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
HEAT1: JP4.12, U1.5 (D_2), U1.6 (D_3), U1.7 (D_4), U1.8 (D)
HEAT2: JP4.14, U2.5 (D_2), U2.6 (D_3), U2.7 (D_4), U2.8 (D)
HEAT3: JP4.16, U3.5 (D_2), U3.6 (D_3), U3.7 (D_4), U3.8 (D)
I2C_SCL: JP3.2, U4.13 (P3.2/UCB0SOMI/UCB0SCL)
I2C_SDA: JP3.1, U4.12 (P3.1/UCB0SIMO/UCB0SDA)
IND: L3.P$2 (2), U8.1 (SW), U8.2 (SW)
I_IN: C8.2, R25.1, U4.9 (P2.1/TAINCLK/SMCLK/A1)
I_OUT: C9.2, R26.1, U4.8 (P2.0/ACLK/A0)
LED5: +5V.C, R15.2
unnamed: L2.P$1 (1), U7.3 (L1)
unnamed: R28.1, U8.5 (PG)
unnamed: L2.P$2 (2), U7.1 (L2)
unnamed: 6.8UH.2, R_SENSE1.I1
unnamed: C13.1, U8.6 (SS)
unnamed: L1.P$1 (1), U6.3 (L1)
unnamed: L1.P$2 (2), U6.1 (L2)
unnamed: L100.P$1 (1), U100.3 (L1)
unnamed: L100.P$2 (2), U100.1 (L2)
unnamed: J5.2, R15.1
unnamed: IC1.1 (OUT), R1.2, R9.1
unnamed: IC1.2 (-IN), R9.2, R10.1
unnamed: IC1.3 (+IN), R21.2, R23.1
unnamed: IC1.7 (OUT), R2.2, R17.1
unnamed: IC1.6 (-IN), R17.2, R18.1
unnamed: IC1.5 (+IN), R20.2, R22.1
unnamed: R26.2, U$3.6 (OUT)
unnamed: R25.2, U$2.6 (OUT)
unnamed: R7.1, U3.4 (G)
unnamed: Q1.P1 (1), U4.6 (XIN/P2.6)
unnamed: R5.1, U2.4 (G)
unnamed: R_SENSE2.V1, U$3.4 (IN+)
unnamed: R_SENSE2.V2, U$3.5 (IN-)
unnamed: RSENSE1.V1, U$2.4 (IN+)
unnamed: RSENSE1.V2, U$2.5 (IN-)
unnamed: Q1.P2 (2), U4.5 (XOUT/P2.7)
unnamed: R3.1, U1.4 (G)
unnamed: C31.2, U$1.P$8 (BOOT)
unnamed: +3V3_M.C, R12.2
unnamed: J2.2, R12.1
unnamed: R11.2, VCC.C
unnamed: J1.2, R11.1
unnamed: +3V3_2.C, R14.2
unnamed: J4.2, R14.1
unnamed: +11V.C, R16.2
unnamed: J6.2, R16.1
unnamed: C31.1, L4.P$2 (2), R39.2, U$1.P$4 (SW1), U$1.P$5 (SW2), U$1.P$6 (SW3), U$1.P$7 (SW4)
unnamed: +3V3_1.C, R13.2
unnamed: J3.2, R13.1
unnamed: R39.1, U$1.P$3 (FSW)
unnamed: C25.1, R37.1
unnamed: C36.1, U$1.P$10 (SS)
unnamed: R35.2, U$1.P$19 (ILIM)
unnamed: C24.1, R37.2, U$1.P$18 (COMP)
unnamed: C23.1, U$1.P$1 (VCC)
unnamed: R36.2, R38.1, U$1.P$17 (FB)
unnamed: Q100.3 (D), R100.2, R101.1, U9.2 (MPPSET)
unnamed: C22.1, R41.1
unnamed: R31.1, STAT1.A
unnamed: J7.2, STAT2.C
unnamed: J8.2, STAT1.C
unnamed: R29.1, STAT2.A
unnamed: J7.1, U9.5 (STAT2)
unnamed: J8.1, U9.3 (STAT1)
unnamed: C20.1, U9.6 (VREF)
unnamed: C21.1, R40.2, U9.1 (VCC)
unnamed: JP2.2, U4.1 (TEST/SBWTCK)
unnamed: 6.8UH.1, C100.1, U9.14 (PH), U10.1 (S_2), U10.2 (S_3), U10.3 (S), U11.5 (D_2), U11.6 (D_3), U11.7 (D_4), U11.8 (D)
unnamed: C15.2, R_SENSE1.V1, U9.10 (SRP)
unnamed: C15.1, R_SENSE1.V2, U9.9 (SRN)
unnamed: U9.15 (HIDRV), U10.4 (G)
unnamed: U9.13 (LODRV), U11.4 (G)
unnamed: C26.2, R32.1, R33.2, R34.1, U9.8 (VFB)
unnamed: C101.1, D1.1 (A1), D1.2 (A2), U9.12 (REGN)
unnamed: C100.2, D1.3 (CC), U9.16 (BTST)
unnamed: JP2.1, R19.1, U4.7 (RST/NMI/SBWTDIO)
unnamed: C3.1, FERRITE.2, U4.16 (AVCC)
SC+: C32.2, JP5.2, R22.2, R29.2, R31.2, R40.1, R41.2, R101.2, R102.2, U10.5 (D_2), U10.6 (D_3), U10.7 (D_4), U10.8 (D)
SC_OUT: C26.1, C37.1, C38.1, R32.2, R34.2, RSENSE1.I1, R_SENSE1.I2
V_BAT: C1.2, R1.1, U4.29 (P2.3/TA1/A3/VREF−/VEREF-)
V_SC: C2.2, R2.1, U4.10 (P2.2/TA0/A2)

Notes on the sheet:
Solar
3.3V
12V
Battery voltage
Solar cell voltage
SOLAR in
Current Out
-> Vout = 11.4 V
456kOhm for R23 for Vout = 11V
1.2V for MPP
1uA leakage
Charge termination disabled
Vterm = 4.1 V -> be nice with battery
10mOhm -> 4A max current
2N7002DICT
Si7288DP as alternative
